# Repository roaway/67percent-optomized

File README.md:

# 67percent-optomized

optomized condenced keyboard for the masses
67% size of a standard 104 key keyboard 
70 keys. 

Project will include a PCB design with either a daughterboard HID device (Teensy 2.0) or build on ATMega(hopefully)

this will become a community project.

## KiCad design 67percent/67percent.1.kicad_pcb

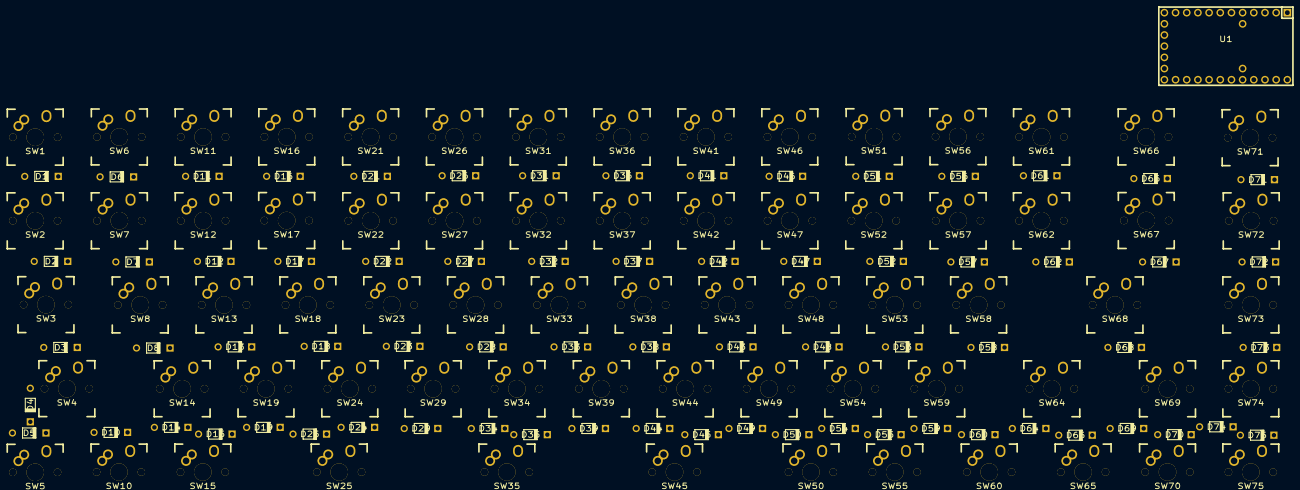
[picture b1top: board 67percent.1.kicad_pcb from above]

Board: 2 copper layers, 141 parts (0 on the bottom side), 90 nets, no tracks yet.

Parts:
D1, D2, D3, D4, D5, D6, D7, D8, D10, D11, D12, D13, D14, D15, D16, D17, D18, D19, D21, D22, D23, D24, D25, D26, D27, D28, D29, D31, D32, D33, D34, D35, D36, D37, D38, D39, D41, D42, D43, D44, D45, D46, D47, D48, D49, D50, D51, D52, D53, D54, D55, D56, D57, D58, D59, D60, D61, D62, D64, D65, D66, D67, D68, D69, D70, D71, D72, D73, D74, D75: D_Small; DIODE
SW1, SW2, SW3, SW4, SW5, SW6, SW7, SW8, SW10, SW11, SW12, SW13, SW14, SW15, SW16, SW17, SW18, SW19, SW21, SW22, SW23, SW24, SW25, SW26, SW27, SW28, SW29, SW31, SW32, SW33, SW34, SW35, SW36, SW37, SW38, SW39, SW41, SW42, SW43, SW44, SW45, SW46, SW47, SW48, SW49, SW50, SW51, SW52, SW53, SW54, SW55, SW56, SW57, SW58, SW59, SW60, SW61, SW62, SW64, SW65, SW66, SW67, SW68, SW69, SW70, SW71, SW72, SW73, SW74, SW75: SPST; MXALPS_100_Plated
U1: TEENSY2.0; TEENSY_2.0

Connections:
unnamed: D1.1, SW1.1
unnamed: D1.2, D6.2, D11.2, D16.2, D21.2, D26.2, D31.2, D36.2, D41.2, D46.2, D51.2, D56.2, D61.2, D66.2, D71.2, U1.27
unnamed: D2.1, SW2.1
unnamed: D3.1, SW3.1
unnamed: D4.1, SW4.1
unnamed: D5.1, SW5.1, U1.5
unnamed: D6.1, SW6.1
unnamed: D7.1, SW7.1
unnamed: D8.1, SW8.1
unnamed: D10.1, SW10.1
unnamed: D5.2, D10.2, D15.2, D25.2, D35.2, D45.2, D50.2, D55.2, D60.2, D65.2, D70.2, D75.2, U1.9
unnamed: D11.1, SW11.1
unnamed: D12.1, SW12.1
unnamed: D2.2, D7.2, D12.2, D17.2, D22.2, D27.2, D32.2, D37.2, D42.2, D47.2, D52.2, D57.2, D62.2, D67.2, D72.2, U1.26
unnamed: D13.1, SW13.1
unnamed: D3.2, D8.2, D13.2, D18.2, D23.2, D28.2, D33.2, D38.2, D43.2, D48.2, D53.2, D58.2, D68.2, D73.2, U1.25
unnamed: D14.1, SW14.1
unnamed: D4.2, D14.2, D19.2, D24.2, D29.2, D34.2, D39.2, D44.2, D49.2, D54.2, D59.2, D64.2, D69.2, D74.2, U1.10
unnamed: D15.1, SW15.1
unnamed: D16.1, SW16.1
unnamed: D17.1, SW17.1
unnamed: D18.1, SW18.1
unnamed: D19.1, SW19.1
unnamed: D21.1, SW21.1
unnamed: D22.1, SW22.1
unnamed: D23.1, SW23.1
unnamed: D24.1, SW24.1
unnamed: D25.1, SW25.1
unnamed: D26.1, SW26.1
unnamed: D27.1, SW27.1
unnamed: D28.1, SW28.1
unnamed: D29.1, SW29.1
unnamed: D31.1, SW31.1
unnamed: D32.1, SW32.1
unnamed: D33.1, SW33.1
unnamed: D34.1, SW34.1
unnamed: D35.1, SW35.1
unnamed: D36.1, SW36.1
unnamed: D37.1, SW37.1
unnamed: D38.1, SW38.1
unnamed: D39.1, SW39.1
unnamed: D41.1, SW41.1
unnamed: D42.1, SW42.1
unnamed: D43.1, SW43.1
unnamed: D44.1, SW44.1
unnamed: D45.1, SW45.1
unnamed: D46.1, SW46.1
unnamed: D47.1, SW47.1
unnamed: D48.1, SW48.1
unnamed: D49.1, SW49.1
unnamed: D50.1, SW50.1
unnamed: D51.1, SW51.1
unnamed: D52.1, SW52.1
unnamed: D53.1, SW53.1
unnamed: D54.1, SW54.1
unnamed: D55.1, SW55.1
unnamed: D56.1, SW56.1
unnamed: D57.1, SW57.1
unnamed: D58.1, SW58.1
unnamed: D59.1, SW59.1
unnamed: D60.1, SW60.1
unnamed: D61.1, SW61.1
unnamed: D62.1, SW62.1
unnamed: D64.1, SW64.1
unnamed: D65.1, SW65.1
unnamed: D66.1, SW66.1
unnamed: D67.1, SW67.1
unnamed: D68.1, SW68.1
unnamed: D69.1, SW69.1
unnamed: D70.1, SW70.1
unnamed: D71.1, SW71.1
unnamed: D72.1, SW72.1
unnamed: D73.1, SW73.1
unnamed: D74.1, SW74.1
unnamed: D75.1, SW75.1
unnamed: SW1.2, SW2.2, SW3.2, SW4.2, SW5.2, U1.4
unnamed: SW6.2, SW7.2, SW8.2, SW10.2, U1.3
unnamed: SW11.2, SW12.2, SW13.2, SW14.2, SW15.2, U1.2
unnamed: SW16.2, SW17.2, SW18.2, SW19.2, U1.31
unnamed: SW21.2, SW22.2, SW23.2, SW24.2, SW25.2, U1.11
unnamed: SW26.2, SW27.2, SW28.2, SW29.2, U1.12
unnamed: SW31.2, SW32.2, SW33.2, SW34.2, SW35.2, U1.17
unnamed: SW36.2, SW37.2, SW38.2, SW39.2, U1.13
unnamed: SW41.2, SW42.2, SW43.2, SW44.2, SW45.2, U1.20
unnamed: SW46.2, SW47.2, SW48.2, SW49.2, SW50.2, U1.21
unnamed: SW51.2, SW52.2, SW53.2, SW54.2, SW55.2, U1.22
unnamed: SW56.2, SW57.2, SW58.2, SW59.2, SW60.2, U1.23
unnamed: SW61.2, SW62.2, SW64.2, SW65.2, U1.18
unnamed: SW66.2, SW67.2, SW68.2, SW69.2, SW70.2, U1.19
unnamed: SW71.2, SW72.2, SW73.2, SW74.2, SW75.2, U1.24

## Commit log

2016-03-07 Rename 70_-optomized.kbd.json to 67_-optomized.kbd.json
2016-03-07 Added files via upload
